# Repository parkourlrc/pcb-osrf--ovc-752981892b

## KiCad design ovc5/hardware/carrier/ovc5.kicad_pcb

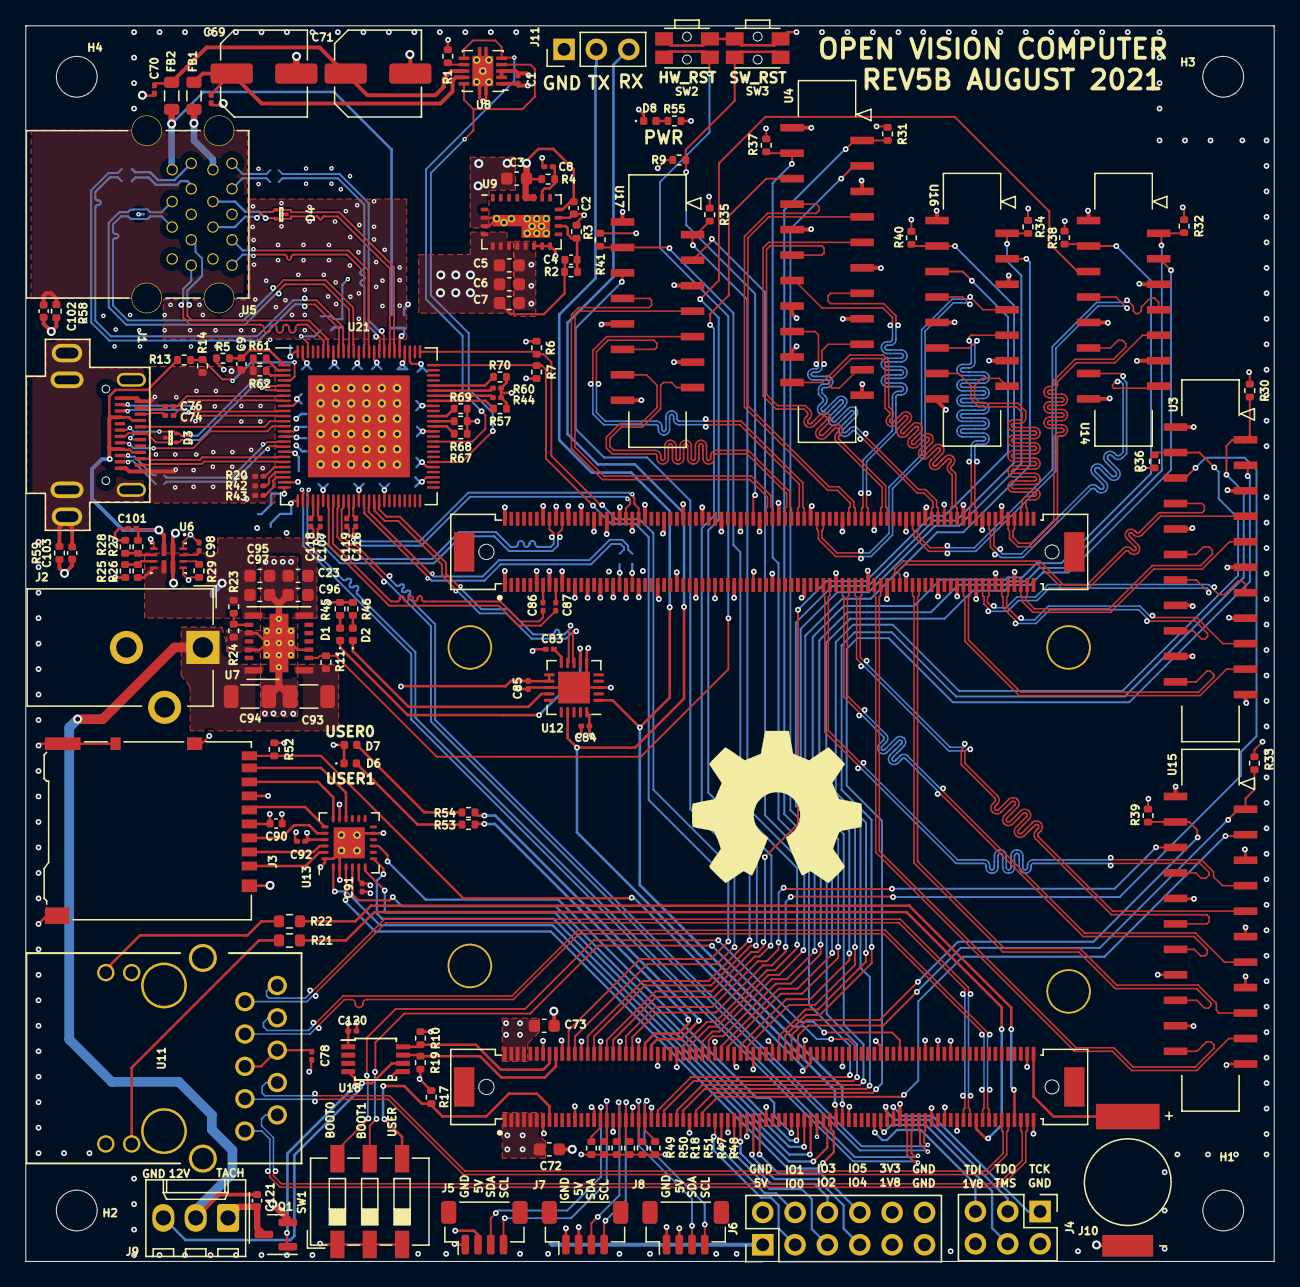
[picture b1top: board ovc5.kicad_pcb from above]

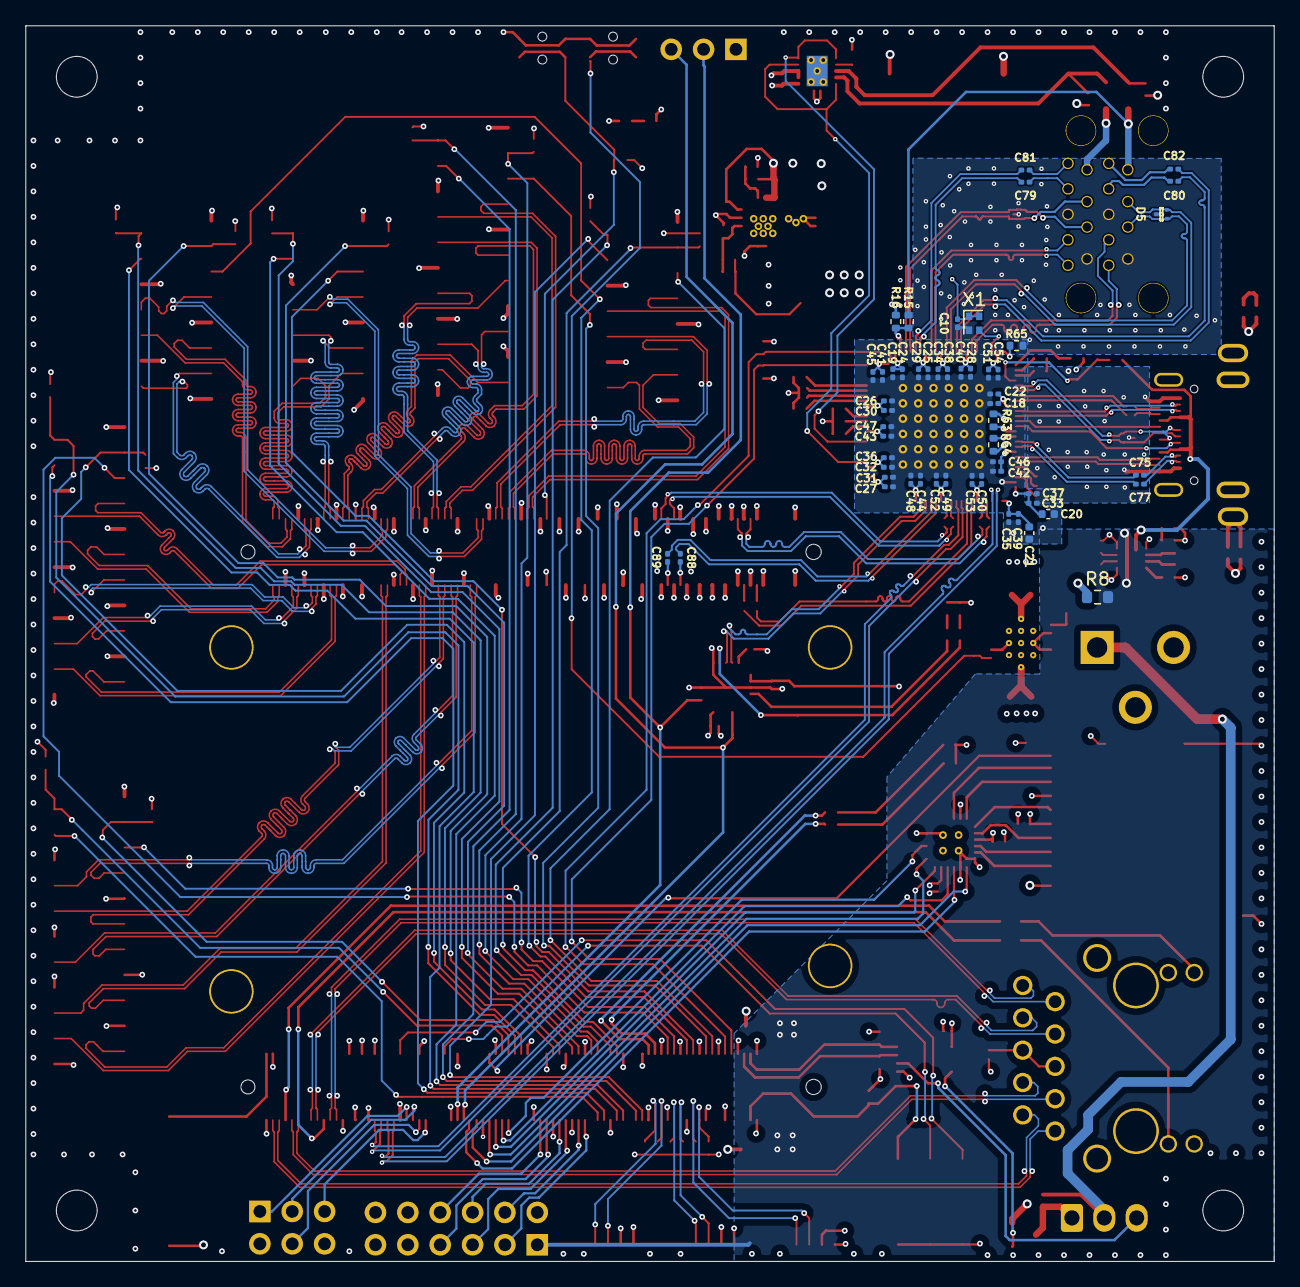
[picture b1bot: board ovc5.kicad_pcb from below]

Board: 6 copper layers, 98.0 x 97.0 mm, 202 parts (53 on the bottom side), 236 nets.

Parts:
C1, C8, C10, C18, C19, C25, C26, C27, C32, C33, C34, C35, C40, C41, C42, C43, C44, C49, C50, C51, C68, C70, C74, C75, C76, C77, C78, C79, C80, C81, C82, C83, C84, C85, C86, C87, C88, C89, C91, C92, C98, C101, C107, C116, C118, C119, C120: 100n; C_0201_0603Metric
C2, C9, C90, C121: 1u; C_0402_1005Metric
C3, C5, C6, C7, C23, C72, C73, C95, C96, C97: 22u; C_0603_1608Metric
C4: 10p; C_0402_1005Metric
C20, C21: 4u7; C_0402_1005Metric
C22, C24, C28, C29, C30, C31, C36, C37, C38, C39, C45, C46, C47, C48, C52, C53, C54: 1n; C_0201_0603Metric
C69, C71: 150u; C_Elec_6.3x7.7
C93, C94: 10u; C_1206_3216Metric
C102, C103: 2n2; C_0402_1005Metric
D1, D2, D6, D7, D8: LED_Small; LED_0402_1005Metric
D3, D4, D5: D_TVS_Dual_AAC; TPD2EUSB30x
FB1, FB2: MH2029-100Y; L_0805_2012Metric
H1, H2, H3, H4: MountingHole; MountingHole_3.2mm_M3
J1: USB_C_Receptacle; Amphenol_12402056E512A
J2: AUX_PWR; BarrelJack_CUI_PJ-102AH_Horizontal
J3: Micro_SD_Card_Det_Hirose_DM3AT; microSD_HC_Hirose_DM3AT-SF-PEJM5
J4: JTAG; PinHeader_2x03_P2.54mm_Vertical
J5, J7, J8: Conn_01x04; JST_SH_BM04B-SRSS-TB_1x04-1MP_P1.00mm_Vertical
J6: Conn_02x06_Odd_Even; PinHeader_2x06_P2.54mm_Vertical
J9: Conn_01x03; Molex_KK-254_AE-6410-03A_1x03_P2.54mm_Vertical
J10: Conn_01x02; ELNA_DSK-3R3H224U-HL
J11: Conn_01x03; PinHeader_1x03_P2.54mm_Vertical
LOGO1: Logo_Open_Hardware_Large; OSHW-Symbol_13.4x12mm_SilkScreen
Q1: Q_NMOS_GSD; SOT-23
R1, R4, R9, R11, R25, R27: 47k; R_0402_1005Metric
R2: 348k; R_0402_1005Metric
R3: 357k; R_0402_1005Metric
R5, R29: 20k; R_0402_1005Metric
R6, R7, R10, R19: 4.7k; R_0402_1005Metric
R8: JMP; R_0603_1608Metric
R13, R15: 43k; R_0402_1005Metric
R14, R16: 49.9k; R_0402_1005Metric
R17, R23, R26, R28, R52, R61, R62, R63, R64, R67, R68, R69: 10k; R_0402_1005Metric
R18, R24, R30, R31, R32, R33, R34, R35, R36, R37, R38, R39, R40, R41, R47, R48, R49, R50, R51: 2k4; R_0402_1005Metric
R20, R42, R43, R44, R60: 200k; R_0201_0603Metric
R21, R22: 110R; R_0603_1608Metric
R45, R46, R53, R54, R55: 220R; R_0402_1005Metric
R57, R58, R59, R70: 100k; R_0402_1005Metric
R65: 12k; R_0402_1005Metric
SW1: SW_DIP_x03; SW_DIP_SPSTx03_Slide_6.7x9.18mm_W6.73mm_P2.54mm_LowProfile_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
SW2: Reset_Hardware; SW_SPST_EVQP7C
SW3: Reset_Software; SW_SPST_EVQP7C
U1: Mercury_XU5_4CG-4EV-5EV; Mercury_XU5
U3, U4, U15: PICAM_Expandable_Reversed; AMPHENOL_SFW22S
U5: USB3_A_Dual_Stacked
U6: TPS2121; Texas_VQFN-HR-12_2x2.5_Pitch0.5mm
U7: TPSM53604RDA; Texas_B3QFN-14-1EP_5x5.5mm_P0.65mm_ThermalVia
U8: TPS2561; VSON-10-1EP_3x3mm_P0.5mm_EP1.65x2.4mm_ThermalVias
U9: EN5339QI; Converter_DCDC_Intel_QFN-24_4x6mm_P0.65mm_ThermalVias
U11: ARJ11C-MBSAS-A-BA-7MU2
U12: FT231XQ; QFN-20-1EP_4x4mm_P0.5mm_EP2.5x2.5mm
U13: TXS02612; TI_RTW0024B
U14, U16, U17: PICAM_Reversed; AMPHENOL_SFW15S
U18: EMC2101-ACZL-TR; TSSOP-8_3x3mm_P0.65mm
U21: USB7216C; Microchip_USB7216C
X1: ASCO; Oscillator_SMD_Abracon_ASCO-4Pin_1.6x1.2mm

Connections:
+1V2: C4.1, C5.1, C6.1, C7.1, C18.1, C20.1, C22.1, C25.1, C28.1, C29.1, C32.1, C33.1, C36.1, C37.1, C40.1, C41.1, C42.1, C45.1, C46.1, C49.1, C50.1, C52.1, C53.1, R2.1, R9.1, U1.B64 (VCC_IO_B65), U1.B67 (VCC_IO_B66), U1.B88 (VCC_IO_B65), U1.B95 (VCC_IO_B66), U1.B140 (VCC_IO_B65), U1.B143 (VCC_IO_B66), U9.4 (VOUT), U9.5 (VOUT), U9.6 (VOUT), U9.7 (VOUT), U21.9 (VCORE), U21.18 (VCORE), U21.25 (VCORE), U21.31 (VCORE), U21.38 (VCORE), U21.55 (VCORE), U21.78 (VCORE), U21.85 (VCORE), U21.93 (VCORE)
+1V8: C84.2, C91.2, J4.6, J6.9, R30.1, R31.1, R32.1, R33.1, R34.1, R35.1, R36.1, R37.1, R38.1, R39.1, R40.1, R41.1, R52.1, U1.A41 (VCC_IO_BO), U1.A74 (VCC_CFG_MIO), U1.A77 (VCC_CFG_MIO), U1.B52 (VOUT_1V8), U1.B76 (VOUT_1V8), U1.B108 (VOUT_1V8), U1.B128 (VOUT_1V8), U12.20 (VCCIO), U13.5 (VCCA)
+3V3: C2.1, C3.1, C10.2, C19.1, C21.1, C24.1, C26.1, C27.1, C30.1, C31.1, C34.1, C35.1, C38.1, C39.1, C43.1, C44.1, C47.1, C48.1, C51.1, C54.1, C90.2, C92.1, C120.2, J3.4 (VDD), J5.2, J6.10, J7.2, J8.2, R4.1, R5.1, R6.2, R7.2, R10.2, R17.1, R18.2, R19.2, R45.1, R46.1, R47.2, R48.2, R49.1, R50.1, R51.1, R55.1, R63.1, R64.1, R67.1, R68.1, R69.1, U1.A26 (VOUT_3V3), U1.A29 (VOUT_3V3), U1.A38 (VCC_IO_BN), U1.A50 (VOUT_3V3), U1.A86 (VOUT_3V3), U1.B55 (VOUT_3V3), U1.B79 (VOUT_3V3), U1.B115 (VOUT_3V3), U1.B127 (VOUT_3V3), U1.B152 (VOUT_3V3), U1.B155 (VOUT_3V3), U3.1 (3V3), U4.1 (3V3), U9.10 (VS2), U9.11 (VS1), U9.12 (VS0), U9.16 (AVIN), U9.19 (PVIN), U9.20 (PVIN), U11.12 (GRNYEL_A), U11.13 (GRN_A), U13.17 (VCCB1), U13.21 (VCCB0), U14.1 (3V3), U15.1 (3V3), U16.1 (3V3), U17.1 (3V3), U18.1 (VDD), U21.26 (VDD33), U21.43 (VDD33), U21.53 (VDD33), U21.62 (VDD33), U21.67 (VDD33), U21.79 (VDD33), U21.88 (VDD33), U21.99 (VDD33), X1.1 (EN), X1.4 (V+)
+5V: C1.1, C72.1, C73.1, C85.1, J6.1, R8.2, U1.A1 (VIN_MOD), U1.A2 (VIN_MOD), U1.A3 (VIN_MOD), U1.A4 (VIN_MOD), U1.A5 (VIN_MOD), U1.A6 (VIN_MOD), U1.A7 (VIN_MOD), U1.A8 (VIN_MOD), U1.A9 (VIN_MOD), U1.A11 (VIN_MOD), U6.1 (OUT), U6.8 (OUT), U8.2 (IN), U8.3 (IN), U12.11 (~RESET), U12.12 (VCC)
+12V: C93.1, C94.1, C121.1, J2.1, J9.2, R11.1, U7.1 (VIN), U7.14 (VIN)
/Enclustra module/BATT: J10.2, U1.A168 (VIN_BAT)
/Enclustra module/JTAG_TCK: J4.1, U1.A123 (JTAG_TCK)
/Enclustra module/JTAG_TDI: J4.5, U1.A117 (JTAG_TDI)
/Enclustra module/JTAG_TDO: J4.3, U1.A121 (JTAG_TDO)
/Enclustra module/JTAG_TMS: J4.4, U1.A119 (JTAG_TMS)
/Enclustra module/USER_LED0: R53.1, U1.A46 (BN_L6_HDGC_AC14_P)
/Enclustra module/USER_LED1: R54.1, U1.A48 (BN_L6_HDGC_AC13_N)
/Interfaces/RXLED: D2.1 (K), U12.14 (CBUS1)
/Interfaces/SD_CLK: J3.5 (CLK), U13.19 (CLKB0)
/Interfaces/SD_CMD: J3.3 (CMD), U13.20 (CMDB0)
/Interfaces/SD_D0: J3.7 (DAT0), U13.18 (DAT0B0)
/Interfaces/SD_D1: J3.8 (DAT1), U13.16 (DAT1B0)
/Interfaces/SD_D2: J3.1 (DAT2), U13.23 (DAT2B0)
/Interfaces/SD_D3: J3.2 (DAT3/CD), U13.22 (DAT3B0)
/Interfaces/TACH: J9.3, U18.6 (ALERT/TACH)
/Interfaces/TXLED: D1.1 (K), U12.7 (CBUS2)
/Power/VREG: C23.1, C95.1, C96.1, C97.1, R8.1, R23.1, R25.1, U6.6 (PR1), U6.7 (IN1), U7.7 (VOUT), U7.8 (VOUT)
/USB/A_SHIELD: C102.2, R58.1, U5.S (Shield)
/USB/C_SHIELD: C103.2, J1.S1 (SHIELD), R59.1
/USB/HUB_DN2_TX+: C118.1, U21.29 (USB3DN2_TX_P)
/USB/HUB_DN2_TX-: C107.1, U21.30 (USB3DN2_TX_N)
/USB/HUB_DN3_TX+: C119.1, U21.36 (USB3DN3_TX_P)
/USB/HUB_DN3_TX-: C116.1, U21.37 (USB3DN3_TX_N)
/USB/OSC_OUT: U21.98 (XTALI/CLK_IN), X1.3 (OUT)
/USB/RESET: C9.1, R5.2, U21.1 (RESET_N)
/USB/USB0_EN_OVC: U8.4 (EN1), U8.10 (~FAULT1), U21.56 (PF13)
/USB/USB1_EN_OVC: U8.5 (EN2), U8.6 (~FAULT2), U21.60 (PF17)
/USB/USB_H0_D_N: D4.2 (A2), U5.11 (D1-), U21.82 (PRT_DIS_M4/USB2DN4_D_N)
/USB/USB_H0_D_P: D4.1 (A1), U5.12 (D1+), U21.81 (PRT_DIS_P4/USB2DN4_D_P)
/USB/USB_H0_RX_N: U5.14 (SSRX1-), U21.87 (USB3DN4_RX_N)
/USB/USB_H0_RX_P: U5.15 (SSRX1+), U21.86 (USB3DN4_RX_P)
/USB/USB_H0_TX_CONN_N: C79.1, U5.17 (SSTX1-)
/USB/USB_H0_TX_CONN_P: C81.1, U5.18 (SSTX1+)
/USB/USB_H0_TX_N: C79.2, U21.84 (USB3DN4_TX_N)
/USB/USB_H0_TX_P: C81.2, U21.83 (USB3DN4_TX_P)
/USB/USB_H1_D_N: D5.2 (A2), U5.2 (D0-), U21.90 (USB2UP_D_N)
/USB/USB_H1_D_P: D5.1 (A1), U5.3 (D0+), U21.89 (USB2UP_D_P)
/USB/USB_H1_RX_N: U5.5 (SSRX0-), U21.95 (USB3UP_RX_N)
/USB/USB_H1_RX_P: U5.6 (SSRX0+), U21.94 (USB3UP_RX_P)
/USB/USB_H1_TX_CONN_N: C80.1, U5.8 (SSTX0-)
/USB/USB_H1_TX_CONN_P: C82.1, U5.9 (SSTX0+)
/USB/USB_H1_TX_N: C82.2, U21.92 (USB3UP_TX_N)
/USB/USB_H1_TX_P: C80.2, U21.91 (USB3UP_TX_P)
/USB/USB_US_CC1_CONN: J1.A5 (CC1), U21.12 (DP1_CC1)
/USB/USB_US_CC2_CONN: J1.B5 (CC2), U21.13 (DP1_CC2)
/USB/USB_US_D_CONN_N: D3.2 (A2), J1.A7 (D-), J1.B7 (D-), U21.5 (PRT_DIS_P1/USB2DN1_D_P)
/USB/USB_US_D_CONN_P: D3.1 (A1), J1.A6 (D+), J1.B6 (D+), U21.6 (PRT_DIS_M1/USB2DN1_D_N)
/USB/USB_US_RX1_CONN_N: J1.B10 (RX1-), U21.11 (USB3DN1_RX1_N)
/USB/USB_US_RX1_CONN_P: J1.B11 (RX1+), U21.10 (USB3DN1_RX1_P)
/USB/USB_US_RX2_CONN_N: J1.A10 (RX2-), U21.19 (USB3DN1_RX2_P)
/USB/USB_US_RX2_CONN_P: J1.A11 (RX2+), U21.20 (USB3DN1_RX2_N)
/USB/USB_US_TX1_CONN_N: C76.1, J1.A2 (TX1+)
/USB/USB_US_TX1_CONN_P: C74.1, J1.A3 (TX1-)
/USB/USB_US_TX1_N: C76.2, U21.7 (USB3DN1_TX1_P)
/USB/USB_US_TX1_P: C74.2, U21.8 (USB3DN1_TX1_N)
/USB/USB_US_TX2_CONN_N: C77.1, J1.B2 (TX2+)
/USB/USB_US_TX2_CONN_P: C75.1, J1.B3 (TX2-)
/USB/USB_US_TX2_N: C77.2, U21.17 (USB3DN1_TX2_N)
/USB/USB_US_TX2_P: C75.2, U21.16 (USB3DN1_TX2_P)
/USB/VBUS_0: FB1.2, U5.10 (VBUS1)
/USB/VBUS_1: FB2.2, R15.2, U5.1 (VBUS0)
/USB/VBUS_MON_P1: R15.1, R16.2, U21.80 (VBUS_MON_UP)
/USB/VBUS_MON_US: R13.1, R14.2, U21.4 (DP1_VBUS_MON)
/USB/VBUS_SW_0: C68.1, C69.1, FB1.1, U8.9 (OUT1)
/USB/VBUS_SW_1: C70.1, C71.1, FB2.1, U8.8 (OUT2)
BOOT_MODE0: SW1.6, U1.A126 (BOOT_MODE0)
BOOT_MODE1: SW1.5, U1.A112 (BOOT_MODE1)
CAM0_CLK+: U1.B123 (B66_L13_GC_D7_P), U3.7 (CLK+)
CAM0_CLK-: U1.B125 (B66_L13_GC_D6_N), U3.8 (CLK-)
CAM0_DAT0+: U1.B151 (B66_L14_GC_E5_P), U3.13 (DAT0+)
CAM0_DAT0-: U1.B153 (B66_L14_GC_D5_N), U3.14 (DAT0-)
CAM0_DAT1+: U1.B163 (B66_L15_AD11_G6_P), U3.10 (DAT1+)
CAM0_DAT1-: U1.B165 (B66_L15_AD11_F6_N), U3.11 (DAT1-)
CAM0_DAT2+: U1.B157 (B66_L16_AD3_G8_P), U3.17 (DAT2+)
CAM0_DAT2-: U1.B159 (B66_L16_AD3_F7_N), U3.18 (DAT2-)
CAM0_DAT3+: U1.B145 (B66_L17_AD10_F8_P), U3.20 (DAT3+)
CAM0_DAT3-: U1.B147 (B66_L17_AD10_E8_N), U3.21 (DAT3-)
CAM0_ENABLE: U1.A42 (BN_L3_AD13_AH13_N), U3.5 (ENABLE)
CAM0_SCL: R36.2, U1.A88 (BE_L7_HDGC_E10_P), U3.3 (SCL)
CAM0_SDA: R30.2, U1.A90 (BE_L7_HDGC_D10_N), U3.2 (SDA)
CAM0_TRIGGER: U1.A61 (BO_L4_AD8_AE10_P), U3.4 (GPIO)
CAM1_CLK+: U1.B110 (B65_L19_AD9_J5_P), U4.7 (CLK+)
CAM1_CLK-: U1.B112 (B65_L19_AD9_J4_N), U4.8 (CLK-)
CAM1_DAT0+: U1.B114 (B65_L20_AD1_J6_P), U4.13 (DAT0+)
CAM1_DAT0-: U1.B116 (B65_L20_AD1_H6_N), U4.14 (DAT0-)
CAM1_DAT1+: U1.B120 (B65_L21_AD8_J7_P), U4.10 (DAT1+)
CAM1_DAT1-: U1.B122 (B65_L21_AD8_H7_N), U4.11 (DAT1-)
CAM1_DAT2+: U1.B136 (B65_L22_AD0_K8_P), U4.17 (DAT2+)
CAM1_DAT2-: U1.B138 (B65_L22_AD0_K7_N), U4.18 (DAT2-)
CAM1_DAT3+: U1.B142 (B65_L23_SCLK_K9_P), U4.20 (DAT3+)
CAM1_DAT3-: U1.B144 (B65_L23_J9_N), U4.21 (DAT3-)
CAM1_ENABLE: U1.A30 (BN_L1_AD15_AE14_N), U4.5 (ENABLE)
CAM1_SCL: R37.2, U1.A64 (BO_L11_AD1_Y9_P), U4.3 (SCL)
CAM1_SDA: R31.2, U1.A66 (BO_L11_AD1_AA8_N), U4.2 (SDA)
CAM1_TRIGGER: U1.A51 (BO_L7_HDGC_AD5_AD10_N), U4.4 (GPIO)
CAM2_CLK+: U1.B130 (B65_L13_GC_L7_P), U14.7 (CLK+)
CAM2_CLK-: U1.B132 (B65_L13_GC_L6_N), U14.8 (CLK-)
CAM2_DAT0+: U1.B154 (B65_L14_GC_M6_P), U14.13 (DAT0+)
CAM2_DAT0-: U1.B156 (B65_L14_GC_L5_N), U14.14 (DAT0-)
CAM2_DAT1+: U1.B160 (B65_L15_AD11_N7_P), U14.10 (DAT1+)
CAM2_DAT1-: U1.B162 (B65_L15_AD11_N6_N), U14.11 (DAT1-)
CAM2_ENABLE: U1.A36 (BN_L4_AD13_AF13_N), U14.5 (ENABLE)
CAM2_SCL: R38.2, U1.A76 (BO_L6_HDGC_AD6_AC12_P), U14.3 (SCL)
CAM2_SDA: R32.2, U1.A78 (BO_L6_HDGC_AD6_AD12_N), U14.2 (SDA)
CAM2_TRIGGER: U1.A57 (BO_L1_AD11_AH10_N), U14.4 (GPIO/NC)
CAM3_CLK+: U1.B101 (B66_L19_AD9_B5_P), U15.7 (CLK+)
CAM3_CLK-: U1.B103 (B66_L19_AD9_A5_N), U15.8 (CLK-)
CAM3_DAT0+: U1.B107 (B66_L20_AD1_C6_P), U15.13 (DAT0+)
CAM3_DAT0-: U1.B109 (B66_L20_AD1_B6_N), U15.14 (DAT0-)
CAM3_DAT1+: U1.B111 (B66_L21_AD8_A7_P), U15.10 (DAT1+)
CAM3_DAT1-: U1.B113 (B66_L21_AD8_A6_N), U15.11 (DAT1-)
CAM3_DAT2+: U1.B129 (B66_L22_AD0_C8_P), U15.17 (DAT2+)
CAM3_DAT2-: U1.B131 (B66_L22_AD0_B8_N), U15.18 (DAT2-)
CAM3_DAT3+: U1.B117 (B66_L23_A9_P), U15.20 (DAT3+)
CAM3_DAT3-: U1.B119 (B66_L23_A8_N), U15.21 (DAT3-)
CAM3_ENABLE: U1.A40 (BN_L3_AD13_AG13_P), U15.5 (ENABLE)
CAM3_SCL: R39.2, U1.A92 (BE_L8_HDGC_E12_P), U15.3 (SCL)
CAM3_SDA: R33.2, U1.A94 (BE_L8_HDGC_D11_N), U15.2 (SDA)
CAM3_TRIGGER: U1.A63 (BO_L4_AD8_AF10_N), U15.4 (GPIO)
CAM4_CLK+: U1.B100 (B65_L16_AD3_P7_P), U16.7 (CLK+)
CAM4_CLK-: U1.B102 (B65_L16_AD3_P6_N), U16.8 (CLK-)
CAM4_DAT0+: U1.B164 (B65_L17_AD10_N9_P), U16.13 (DAT0+)
CAM4_DAT0-: U1.B166 (B65_L17_AD10_N8_N), U16.14 (DAT0-)
CAM4_DAT1+: U1.B148 (B65_L18_AD2_M8_P), U16.10 (DAT1+)
CAM4_DAT1-: U1.B150 (B65_L18_AD2_L8_N), U16.11 (DAT1-)
CAM4_ENABLE: U1.A34 (BN_L4_AD12_AE13_P), U16.5 (ENABLE)
CAM4_SCL: R40.2, U1.A70 (BO_L10_AD2_W10_P), U16.3 (SCL)
CAM4_SDA: R34.2, U1.A72 (BO_L10_AD2_Y10_N), U16.2 (SDA)
CAM4_TRIGGER: U1.A55 (BO_L1_AD11_AG10_P), U16.4 (GPIO/NC)
CAM5_CLK+: U1.B84 (B65_L7_AD13_L1_P), U17.7 (CLK+)
CAM5_CLK-: U1.B86 (B65_L7_AD13_K1_N), U17.8 (CLK-)
CAM5_DAT0+: U1.B90 (B65_L8_AD5_J1_P), U17.13 (DAT0+)
CAM5_DAT0-: U1.B92 (B65_L8_AD5_H1_N), U17.14 (DAT0-)
CAM5_DAT1+: U1.B94 (B65_L9_AD12_K2_P), U17.10 (DAT1+)
CAM5_DAT1-: U1.B96 (B65_L9_AD12_J2_N), U17.11 (DAT1-)
CAM5_ENABLE: U1.A28 (BN_L1_AD15_AE15_P), U17.5 (ENABLE)
CAM5_SCL: R41.2, U1.A58 (BO_L9_AD3_AA11_P), U17.3 (SCL)
CAM5_SDA: R35.2, U1.A60 (BO_L9_AD3_AA10_N), U17.2 (SDA)
CAM5_TRIGGER: U1.A49 (BO_L7_HDGC_AD5_AD11_P), U17.4 (GPIO/NC)
DEBUG_UART_RX: J11.3, U1.A105 (MIO38_UARTRX), U12.17 (TXD)
DEBUG_UART_TX: J11.2, U1.A107 (MIO39_UARTTX), U12.1 (RXD)
FPGA_FAN_CLK: R10.1, U1.A16 (BN_L8_HDGC_AB15_P), U18.8 (SMCLK)
FPGA_FAN_DATA: R19.1, U1.A18 (BN_L8_HDGC_AB14_N), U18.7 (SMDATA)
FPGA_USB0_D+: U1.A127 (USB0_D_P), U21.27 (PRT_DIS_P2/USB2DN2_D_P)
FPGA_USB0_D-: U1.A129 (USB0_D_N), U21.28 (PRT_DIS_M2/USB2DN2_D_N)
FPGA_USB0_RX+: C107.2, U1.B16 (MGTPS_RX0_F27_P)
FPGA_USB0_RX-: C118.2, U1.B20 (MGTPS_RX0_F28_N)
FPGA_USB0_TX+: C86.1, U21.33 (USB3DN2_RX_N)
FPGA_USB0_TX-: C87.1, U21.32 (USB3DN2_RX_P)
FPGA_USB1_D+: U1.A131 (USB1_D_P), U21.34 (PRT_DIS_P3/USB2DN3_D_P)
FPGA_USB1_D-: U1.A133 (USB1_D_N), U21.35 (PRT_DIS_M3/USB2DN3_D_N)
FPGA_USB1_RX+: C119.2, U1.B40 (MGTPS_RX3_A25_P)
FPGA_USB1_RX-: C116.2, U1.B44 (MGTPS_RX3_A26_N)
FPGA_USB1_TX+: C88.1, U21.39 (USB3DN3_RX_P)
FPGA_USB1_TX-: C89.1, U21.40 (USB3DN3_RX_N)
GBE_LED_ACT: R21.2, U1.A149 (ETH0_LED1n)
GBE_LED_LINK: R22.2, U1.A161 (ETH0_LED2n)
GBE_MDI0_N: U1.A163 (ETH0_A_N), U11.2 (TRD0-)
GBE_MDI0_P: U1.A165 (ETH0_A_P), U11.1 (TRD0+)
GBE_MDI1_N: U1.A157 (ETH0_B_N), U11.4 (TRD1-)
GBE_MDI1_P: U1.A159 (ETH0_B_P), U11.3 (TRD1+)
GBE_MDI2_N: U1.A151 (ETH0_C_N), U11.7 (TRD2+)
GBE_MDI2_P: U1.A153 (ETH0_C_P), U11.8 (TRD2-)
GBE_MDI3_N: U1.A145 (ETH0_D_N), U11.9 (TRD3+)
GBE_MDI3_P: U1.A147 (ETH0_D_P), U11.10 (TRD3-)
GND: C1.2, C2.2, C3.2, C5.2, C6.2, C7.2, C8.2, C9.2, C10.1, C18.2, C19.2, C20.2, C21.2, C22.2, C23.2, C24.2, C25.2, C26.2, C27.2, C28.2, C29.2, C30.2, C31.2, C32.2, C33.2, C34.2, C35.2, C36.2, C37.2, C38.2, C39.2, C40.2, C41.2, C42.2, C43.2, C44.2, C45.2, C46.2, C47.2, C48.2, C49.2, C50.2, C51.2, C52.2, C53.2, C54.2, C68.2, C69.2, C70.2, C71.2, C72.2, C73.2, C78.2, C83.1, C84.1, C85.2, C90.1, C91.1, C92.2, C93.2, C94.2, C95.2, C96.2, C97.2, C98.2, C101.2, C102.1, C103.1, C120.1, D3.3 (common), D4.3 (common), D5.3 (common), D6.1 (K), D7.1 (K), D8.1 (K), J1.A1 (GND), J1.A12 (GND), J1.B1 (GND), J1.B12 (GND), J2.2, J2.3, J3.6 (VSS), J3.10 (DET_A), J3.11 (SHIELD), J4.2, J5.1, J6.2, J6.11, J6.12, J7.1, J8.1, J10.1, J11.1, Q1.2 (S), R1.2, R3.2, R14.1, R16.1, R20.1, R24.2, R26.2, R28.2, R29.2, R42.1, R43.1, R44.1, R57.1, R58.2, R59.2, R60.1, R61.2, R62.2, R65.1, R70.1, SW1.1, SW1.2, SW1.3, SW2.2, SW3.2, U1.A13 (GND), U1.A14 (GND), U1.A20 (GND), U1.A23 (GND), U1.A32 (GND), U1.A35 (GND), U1.A44 (GND), U1.A47 (GND), U1.A56 (GND), U1.A59 (GND), U1.A68 (GND), U1.A71 (GND), U1.A80 (GND), U1.A83 (GND), U1.A96 (GND), U1.A99 (GND), U1.A108 (GND), U1.A109 (GND), U1.A120 (GND), U1.A125 (GND), U1.A134 (GND), U1.A135 (GND), U1.A138 (GND), U1.A139 (GND), U1.A142 (GND), U1.A143 (GND), U1.A166 (GND), U1.A167 (GND), U1.B1 (GND), U1.B2 (GND), U1.B11 (GND), U1.B14 (GND), U1.B15 (GND), U1.B18 (GND), U1.B19 (GND), U1.B22 (GND), U1.B23 (GND), U1.B26 (GND), U1.B27 (GND), U1.B30 (GND), U1.B31 (GND), U1.B34 (GND), U1.B35 (GND), U1.B38 (GND), U1.B39 (GND), U1.B42 (GND), U1.B43 (GND), U1.B46 (GND), U1.B49 (GND), U1.B58 (GND), U1.B61 (GND), U1.B70 (GND), U1.B73 (GND), U1.B82 (GND), U1.B85 (GND), U1.B98 (GND), U1.B105 (GND), U1.B118 (GND), U1.B121 (GND), U1.B134 (GND), U1.B137 (GND), U1.B146 (GND), U1.B149 (GND), U1.B158 (GND), U1.B161 (GND), U3.6 (GND), U3.9 (GND), U3.12 (GND), U3.15 (GND), U3.16 (GND/PAD), U3.19 (GND), U3.22 (GND), U4.6 (GND), U4.9 (GND), U4.12 (GND), U4.15 (GND), U4.16 (GND/PAD), U4.19 (GND), U4.22 (GND), U5.4 (GND0), U5.7 (GND0), U5.13 (GND1), U5.16 (GND1), U6.3 (CP2), U6.9 (ST), U6.12 (GND), U7.3 (PGND), U7.10 (PGND), U7.11 (PGND), U7.12 (AGND), U7.15 (PGND), U8.1 (GND), U8.11 (PAD), U9.2 (PGND), U9.3 (PGND), U9.8 (PGND), U9.9 (PGND), U9.15 (AGND), U9.25 (PGND), U11.MNT, U11.SHLD, U12.3 (GND), U12.6 (~CTS), U12.13 (GND), U12.21 (GND), U13.2 (GND), U13.11 (GND), U13.24 (SEL), U13.25 (PAD), U14.6 (GND), U14.9 (GND), U14.12 (GND), U14.15 (GND), U15.6 (GND), U15.9 (GND), U15.12 (GND), U15.15 (GND), U15.16 (GND/PAD), U15.19 (GND), U15.22 (GND), U16.6 (GND), U16.9 (GND), U16.12 (GND), U16.15 (GND), U17.6 (GND), U17.9 (GND), U17.12 (GND), U17.15 (GND), U18.5 (GND), U21.24 (TESTEN), U21.101 (GND), X1.2 (GND)
GPIO0: J6.3, U1.A67 (BO_L3_AD9_AH12_P)
GPIO1: J6.4, U1.A69 (BO_L3_AD9_AH11_N)
GPIO2: J6.5, U1.A73 (BO_L2_AD10_AF11_P)
GPIO3: J6.6, U1.A75 (BO_L2_AD10_AG11_N)
GPIO4: J6.7, U1.A79 (BO_L12_AD0_AB10_P)
GPIO5: J6.8, U1.A81 (BO_L12_AD0_AB9_N)
unnamed: C4.2, R2.2, R3.1, U9.14 (VFB)
unnamed: C8.1, R4.2, U9.18 (ENABLE)
unnamed: C78.1, U11.5 (CT), U11.6 (CT)
unnamed: C83.2, U12.10 (3V3OUT)
unnamed: C86.2, U1.B13 (MGTPS_TX0_E25_P)
unnamed: C87.2, U1.B17 (MGTPS_TX0_E26_N)
unnamed: C88.2, U1.B37 (MGTPS_TX3_B23_P)
unnamed: C89.2, U1.B41 (MGTPS_TX3_B24_N)
unnamed: C98.1, U6.11 (SS)
unnamed: C121.2, J9.1, Q1.3 (D)
unnamed: D1.2 (A), R45.2
unnamed: D2.2 (A), R46.2
unnamed: D6.2 (A), R53.2
unnamed: D7.2 (A), R54.2
unnamed: D8.2 (A), R55.2
unnamed: Q1.1 (G), U18.4 (FAN)
unnamed: R1.1, U8.7 (ILM)
unnamed: R20.2, U21.21 (CFG_STRAP1)
unnamed: R21.1, U11.11 (GRNYEL_C)
unnamed: R22.1, U11.14 (GRN_C)
unnamed: R23.2, R24.1, U7.9 (FB)
unnamed: R25.2, R26.1, U6.5 (OV1)
unnamed: R27.2, R28.1, U6.4 (OV2)
unnamed: R29.1, U6.10 (ILIM)
unnamed: R42.2, U21.22 (CFG_STRAP2)
unnamed: R43.2, U21.23 (CFG_STRAP3)
unnamed: R44.2, U21.69 (SPI_CE_N/CFG_NON_REM/PF20)
unnamed: R57.2, U21.68 (SPI_CLK/PF21)
unnamed: R60.2, U21.70 (SPI_D0/CFG_BC_EN/PF22)
unnamed: R61.1, U21.2 (PF30)
unnamed: R62.1, U21.3 (PF31)
unnamed: R63.2, U21.14 (PRT_DIS_P5/USB2DN5_D_P)
unnamed: R64.2, U21.15 (PRT_DIS_M5/USB2DN5_D_N)
unnamed: R65.2, U21.100 (RBIAS)
unnamed: R67.2, U21.63 (TEST1)
unnamed: R68.2, U21.64 (TEST2)
unnamed: R69.2, U21.65 (TEST3)
unnamed: R70.2, U21.71 (SPI_D1/PF23)
QWIIC0_SCL: J5.4, R18.1, U1.A33 (BN_L2_AD14_AH14_N)
QWIIC0_SDA: J5.3, R49.2, U1.A31 (BN_L2_AD14_AG14_P)
QWIIC1_SCL: J7.4, R47.1, U1.A39 (BN_L7_HDGC_AB13_N)
QWIIC1_SDA: J7.3, R50.2, U1.A37 (BN_L7_HDGC_AA13_P)
QWIIC2_SCL: J8.4, R48.1, U1.A45 (BN_L5_HDGC_AD14_N)
QWIIC2_SDA: J8.3, R51.2, U1.A43 (BN_L5_HDGC_AD15_P)
REG_EN: R11.2, SW2.1, U7.2 (EN)
SDIO_CDn: J3.9 (DET_B), R52.2, U1.A98 (MIO45_SDCDn)
SDIO_CLK: U1.A91 (MIO51_SDCLK), U13.9 (CLKA)
SDIO_CMD: U1.A93 (MIO50_SDCMD), U13.4 (CMDA)
SDIO_D0: U1.A95 (MIO46_SDD0), U13.6 (DAT0A)
SDIO_D1: U1.A97 (MIO47_SDD1), U13.7 (DAT1A)
SDIO_D2: U1.A101 (MIO48_SDD2), U13.1 (DAT2A)
SDIO_D3: U1.A103 (MIO49_SDD3), U13.3 (DAT3A)
SMBUS_CLK: R7.1, U1.A22 (BN_L11_AD9_W12_P), U21.75 (PF26/1_I2C_CLK/2_I2S_SCK)
SMBUS_DAT: R6.1, U1.A24 (BN_L11_AD9_W11_N), U21.76 (PF27/1_I2C_DAT/2_PRT_CTL6)
SOFTWARE_RESET: R9.2, SW3.1, U1.B80 (B65_L12_GC_L2_N)
USB_UART_D+: U12.8 (USBDP), U21.41 (PRT_DIS_P6/USB2DN6_D_P)
USB_UART_D-: U12.9 (USBDM), U21.42 (PRT_DIS_M6/USB2DN6_D_N)
USER_DIP: R17.2, SW1.4, U1.A15 (BN_L9_AD11_W14_P)
VBUS: C101.1, J1.A4 (VBUS), J1.A9 (VBUS), J1.B4 (VBUS), J1.B9 (VBUS), R13.2, R27.1, U6.2 (IN2)
